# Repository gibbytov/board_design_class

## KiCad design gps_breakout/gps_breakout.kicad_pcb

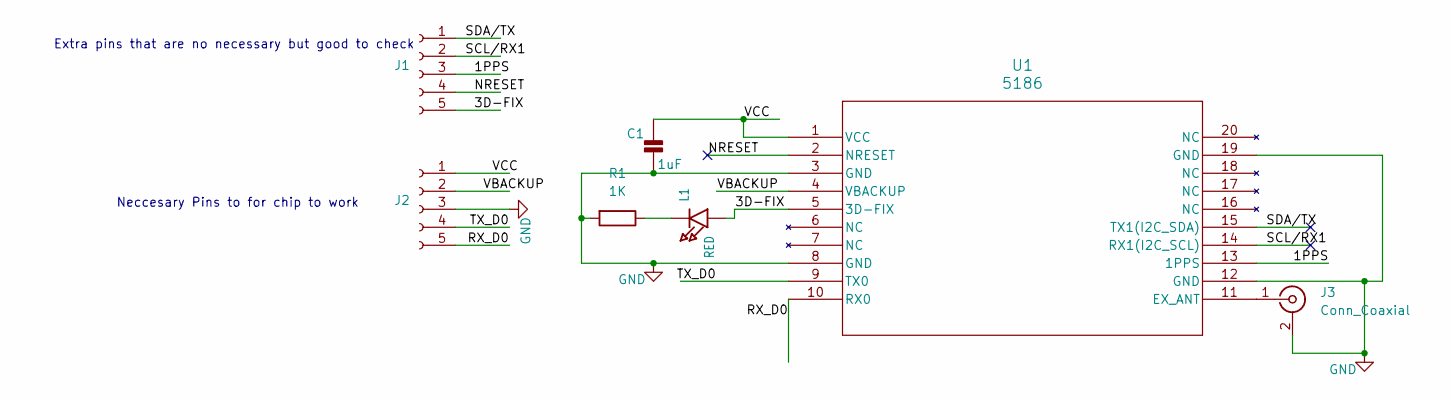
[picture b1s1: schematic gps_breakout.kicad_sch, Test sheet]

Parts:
C1: 1uF; C_0603_1608Metric_Pad1.08x0.95mm_HandSolder; Mfr P/N CC0603KRX7R7BB105
J1, J2: PinHeader_1x05_P2.54mm_Vertical; Mfr P/N M20-9772646
J3: Conn_Coaxial; SMA_Molex_73251-1153_EdgeMount_Horizontal; Mfr P/N CT-SAD12X-006M
L1: RED; CHIPLED_0805_NOOUTLINE; Mfr P/N LTST-S220KRKT
R1: 1K; RC0402N_YAG; Mfr P/N RC0402JR-071KL
U1: 5186; CD-PA1616D_ADA; Mfr P/N 5186

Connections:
/1PPS: J1.3, U1.13 (1PPS)
/3D-FIX: J1.5, L1.A, U1.5 (3D-FIX)
/NRESET: J1.4, U1.2 (NRESET)
/RX_D0: J2.5, U1.10 (RX0)
/SCL/RX1: J1.2, U1.14 (RX1(I2C_SCL))
/SDA/TX: J1.1, U1.15 (TX1(I2C_SDA))
/TX_D0: J2.4, U1.9 (TX0)
/VBACKUP: J2.2, U1.4 (VBACKUP)
/VCC: C1.1, J2.1, U1.1 (VCC)
GND: C1.2, J2.3, J3.2 (Ext), R1.2, U1.3 (GND), U1.8 (GND), U1.12 (GND), U1.19 (GND)
unnamed: J3.1 (In), U1.11 (EX_ANT)
unnamed: L1.C, R1.1

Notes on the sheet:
Extra pins that are no necessary but good to check
Neccesary Pins to for chip to work

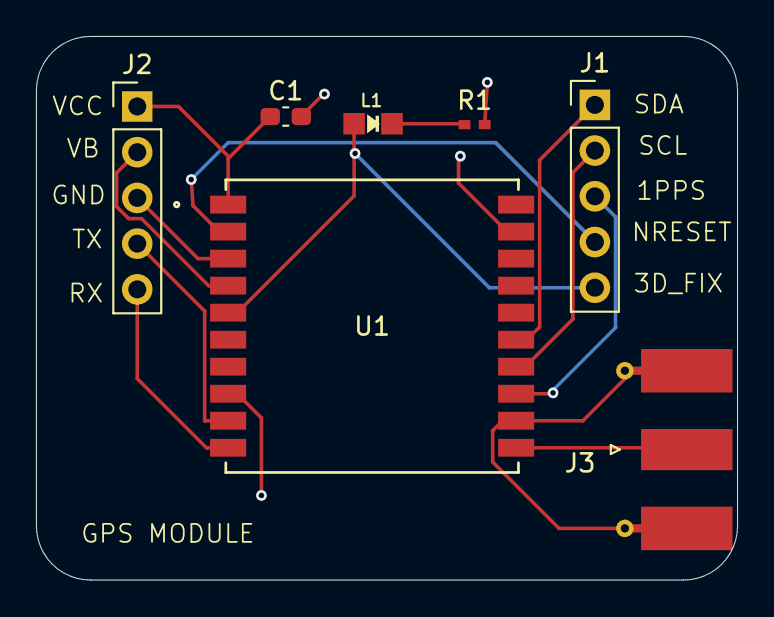
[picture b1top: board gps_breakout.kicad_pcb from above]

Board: 2 copper layers, 38.9 x 30.2 mm, 7 parts (0 on the bottom side), 12 nets.

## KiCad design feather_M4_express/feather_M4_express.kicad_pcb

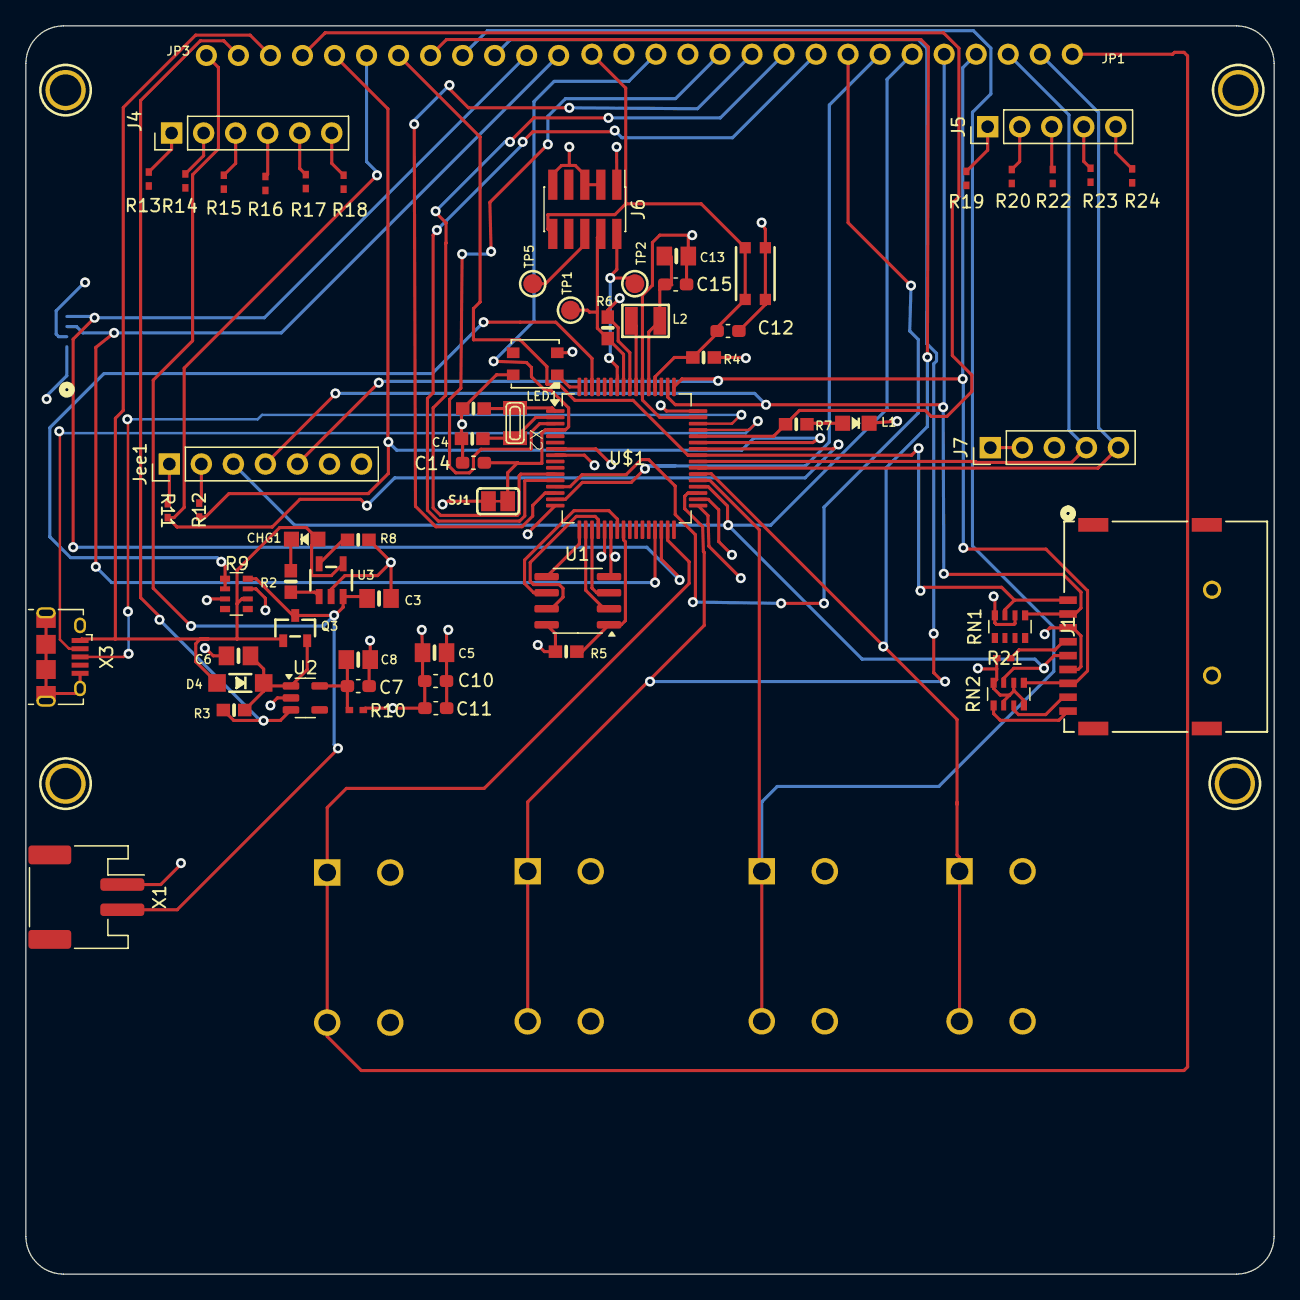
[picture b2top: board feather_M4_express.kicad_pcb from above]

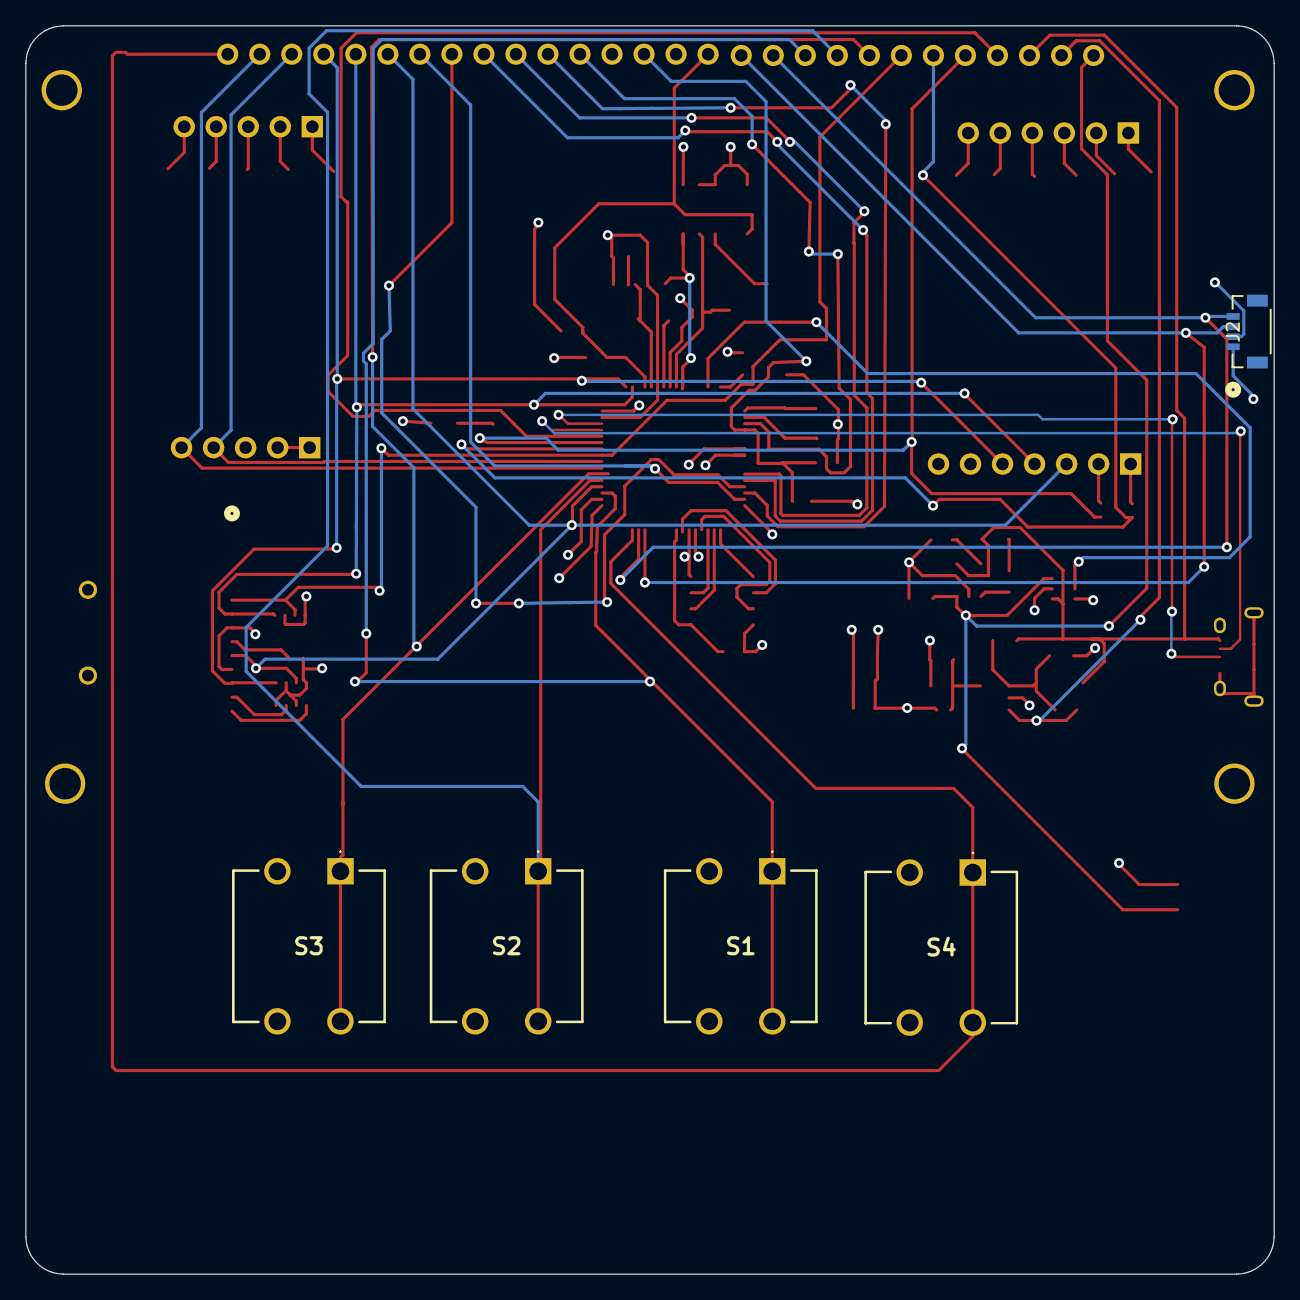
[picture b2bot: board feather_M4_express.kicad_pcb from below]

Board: 4 copper layers, 99.0 x 99.0 mm, 73 parts (5 on the bottom side), 67 nets.

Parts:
C2, C4: 22pF; 0603-NO
C3, C5, C6, C8, C13: 10µF; 0805-NO
C7, C10, C11, C12, C14, C15: 1uF; C_0603_1608Metric_Pad1.08x0.95mm_HandSolder
CHG1: ORANGE; CHIPLED_0805_NOOUTLINE
D4: MBR120; SOD-123
J1: MEM2075-00-140-01-A; MEM2075-00-140-01-A_GCT
J2: Conn_01x04; CONN4X1_DF52-4S-0.8H21_HIR
J4: Conn_01x06_Pin; PinHeader_1x06_P2.54mm_Vertical
J5, J7: Conn_01x05_Pin; PinHeader_1x05_P2.54mm_Vertical
J6: PinHeader_2x05_P1.27mm_Vertical_SMD
JP1: Conn_01x16; 1X16_ROUND
JP3: Conn_01x12; 1X12_ROUND
Jee1: Conn_01x07_Pin; PinHeader_1x07_P2.54mm_Vertical
L1: RED; CHIPLED_0805_NOOUTLINE
L2: 10uH; INDUCTOR_1007
LED1: WS2812B3535; LED3535
P$1, P$2, P$3, P$4: MountingHole; MOUNTINGHOLE_2.5_PLATED
Q3: DMP2070UQ-7; SOT23-R
R2: 1K; 0603-NO
R3, R4, R5, R6, R8: 10K; 0603-NO
R7: 2.2K; 0603-NO
R9: 100K; R_Array_Convex_4x0603
R10, R11, R12, R13, R14, R15, R16, R17, R18, R19, R20, R21, R22, R23, R24: 0 R; RES_1005_SAM
RN1, RN2: R_Pack04_SIP; R_Array_Convex_4x0603
S1, S2, S3, S4: PRT-14460; PRT14460
SJ1: SOLDERJUMPERCLOSED; SOLDERJUMPER_CLOSEDWIRE
SW1: KMR2; BTN_KMR2_4.6X2.8
TP1, TP2, TP5: TESTPOINTROUND1.5MM; TESTPOINT_ROUND_1.5MM
U1: 2MB Flash; SOIC-8_3.9x4.9mm_P1.27mm
U2: AP2112-3.3; SOT-23-5
U3: MCP73831T-2ACI/OT; SOT23-5
U$1: ATSAMD51J19A-AUT; TQFP-64_10x10mm_P0.5mm
X1: JSTPH; JST_PH_S2B-PH-SM4-TB_1x02-1MP_P2.00mm_Horizontal
X2: 32.768 kHz; XTAL3215
X3: microUSB 2.0 B; USB_Micro-B_Amphenol_10118194_Horizontal

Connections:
+3V3: C5.1, C10.1, C11.1, J2.2, J6.1, J7.1, J7.2, JP1.15, Jee1.7, LED1.2 (VDD), R4.1, R5.1, R6.1, R10.1, R21.1, RN1.6 (R3.2), RN1.8 (R4.2), RN2.2 (R1.2), RN2.4 (R2.2), RN2.6 (R3.2), RN2.8 (R4.2), SJ1.2, U1.8 (VCC), U$1.8 (VDDANA), U$1.16 (PA07/I7/AIN7/SERCOM0.3), U$1.21 (VDDIO_0), U$1.34 (VDDIO_1), U$1.48 (VDDIO_2), U$1.56 (VDDIO_3)
/1PPS: J5.3, R22.1
/3D-FIX: J5.5, R24.1
/A0: JP1.12, U$1.3 (PA02/EINT2/AIN0/VOUT0)
/A1: JP1.11, U$1.14 (PA05/I5/AIN5/VOUT1/SERCOM0.1)
/A2: JP1.10, U$1.11 (PB08/I8/AIN2/SERCOM4.0)
/A3: JP1.9, U$1.12 (PB09/I9/AIN3/SERCOM4.1)
/A4: JP1.8, U$1.13 (PA04/I4/VREFB/AIN4/SERCOM0.0)
/A5: JP1.7, U$1.15 (PA06/I6/VREFC/AIN6/SERCOM0.2)
/AREF: C14.1, JP1.14, SJ1.1, U$1.4 (PA03/I3/VREFA/AIN1)
/D4: JP1.1, S4.1, S4.2, U$1.31 (PA14/I14/SERCOM2+4.2)
/D5: JP3.10, S1.1, S1.2, U$1.35 (PA16/I2C/I0/SERCOM1.0+3.1)
/D6: JP3.9, S2.1, S2.2, U$1.37 (PA18/I2/SERCOM1+3.2)
/D8_NEOPIX: LED1.1 (DI), U$1.64 (PB03/I3/AIN15/SERCOM5.1)
/D9: JP3.8, S3.1, S3.2, U$1.38 (PA19/I3/SERCOM1+3.3)
/D10: J1.P1 (DAT2), JP3.7, RN1.7 (R4.1), U$1.41 (PA20/I4/SERCOM3+5.2/I2SFS0)
/D11: JP3.6, R11.2, U$1.42 (PA21/I5/SERCOM3+5.3/I2SDO)
/D12: JP3.5, R12.1, U$1.43 (PA22/I2C/16/SERCOM3.0+5.1/I2SDI)
/D13: JP3.4, R7.1, U$1.44 (PA23/I2C/I7/SERCOM3.1+5.0/SOF/I2SFS1)
/D+: U$1.46 (PA25/19/SERCOM3+5.3/D+), X3.3 (D+)
/D-: U$1.45 (PA24/I8/SERCOM3+5.2/D-), X3.2 (D-)
/EN: JP3.2, R3.2, U2.3 (EN)
/G1: J4.5, R17.1
/G2: J4.4, R16.1
/G3: J4.3, R15.1
/G4: J4.2, R14.1
/G5: J4.1, R13.1
/MISO: J1.P7 (DAT0), JP1.4, Jee1.5, RN2.5 (R3.1), U$1.49 (PB22/I6/SERCOM1+5.2)
/MOSI: J1.P2 (CD/DAT3), JP1.5, Jee1.4, RN1.5 (R3.1), U$1.50 (PB23/I7/SERCOM1+5.3)
/NRESET: J5.4, R23.1
/QSPI_CS: R5.2, U1.1 (SSEL), U$1.24 (PB11/I11/SERCOM4.3/I2SFS1)
/QSPI_DATA[0]: U1.5 (MOSI), U$1.17 (PA08/I2C/AIN8/SERCOM0.0+2.1/I2SMCK)
/QSPI_DATA[1]: U1.2 (MISO), U$1.18 (PA09/I2C/I9/AIN9/SERCOM0.1+2.0/I2SFS0)
/QSPI_DATA[2]: U1.3 (WP#/IO2), U$1.19 (PA10/I10/AIN10/SERCOM0+2.2/I2SCK)
/QSPI_DATA[3]: U1.7 (HOLD#/IO3), U$1.20 (PA11/I11/AIN11/SERCOM0+2.3/I2SDO)
/QSPI_SCK: U1.6 (SCK), U$1.23 (PB10/I10/SERCOM4.2/I2SDI)
/RST: J4.6, R18.1
/RX_D0: J7.4, JP1.3, U$1.40 (PB17/SERCOM5.1/I2SMCK0)
/SCK: J1.P5 (CLK), JP1.6, Jee1.3, RN2.7 (R4.1), U$1.36 (PA17/I2C/I1/SERCOM1.1+3.0)
/SCL: J2.4, JP3.11, U$1.30 (PA13/I13/I2C/SERCOM2.1+4.0)
/SCL/RX1: J5.2, R20.1
/SDA: J2.3, JP3.12, U$1.29 (PA12/I12/I2C/SERCOM2.0+4.1)
/SDA/TX: J5.1, R19.1
/SWCLK: J6.4, R6.2, TP1.P$1, U$1.57 (PA30/I14/SERCOM1.2/SWCLK)
/SWDIO: J6.2, TP2.P$1, U$1.58 (PA31/I15/SERCOM1.3/SWDIO)
/SWO: J6.6, TP5.P$1
/TX_D1: J7.5, JP1.2, U$1.39 (PB16/I0/SERCOM5.0/I2SCK0)
/V_DIV: R9.1, R9.2 (1), U$1.62 (PB01/I1/AIN13/SERCOM5.3)
/Vin: C6.1, D4.C, Q3.2 (S), R3.1, U2.1 (VIN)
/~RESET: C12.1, J6.10, JP1.16, R4.2, SW1.A, SW1.A' (P1), U$1.52 (~RESET)
GND: C2.2, C3.2, C4.2, C5.2, C6.2, C7.2, C8.2, C10.2, C11.2, C12.2, C13.2, C14.2, C15.2, J1.P3 (CMD), J1.P6 (VSS), J2.1, J6.3, J6.5, J6.9, J7.3, JP1.13, Jee1.6, L1.C, LED1.4 (GND), R8.2, R9.3 (1), R9.7 (2), S1.3, S1.4, S2.3, S2.4, S3.3, S3.4, S4.3, S4.4, SW1.B (S), SW1.B' (S1), U1.4 (VSS), U2.2 (GND), U3.2 (VSS), U$1.7 (GND_0), U$1.22 (GND_1), U$1.33 (GND_2), U$1.47 (GND_3), U$1.54 (GND_4), X1.1, X3.5 (GND), X3.6 (Shield)
unnamed: CHG1.C, R2.1
unnamed: J1.P9 (CD), RN2.1 (R1.1)
unnamed: J1.P8 (DAT1), RN2.3 (R2.1)
unnamed: J1.P4 (VDD), R21.2
unnamed: Jee1.1, R11.1
unnamed: Jee1.2, R12.2
unnamed: L1.A, R7.2
unnamed: C13.1, C15.1, L2.P$1 (1), U$1.53 (VDDCORE)
unnamed: L2.P$2 (2), U$1.55 (VSW)
unnamed: C7.1, C8.1, R10.2, U2.5 (VOUT)
unnamed: R8.1, U3.5 (PROG)
unnamed: R2.2, U3.1 (STAT)
unnamed: C2.1, U$1.1 (PA00/EINT0/SERCOM1.0), X2.P$1
unnamed: C4.1, U$1.2 (PA01/EINT1/SERCOM1.1), X2.P$2
VBAT: C3.1, JP3.1, Q3.3 (D), R9.8 (2), U3.3 (VBAT), X1.2
VBUS: CHG1.A, D4.A, JP3.3, Q3.1 (G), R9.6 (2), U3.4 (VDD), X3.1 (VBUS)

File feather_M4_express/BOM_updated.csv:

"Reference","Value","Qty","DNP","Mfr","Mfr P/N","Supplier_1","Supplier_1 P/N","Supplier_1 Unit Price","Supplier 1","Supplier 1 P/N","Supplier 1 Price @ Qty"
"C2,C4","22pF","2","","KEMET","C0603C220K4GAC7867","Digikey","399-C0603C220K4GAC7867CT-ND","0.10","","",""
"C3,C5,C6,C8,C13","10µF","5","","Samsung Electro-Mechanics","CL21A106KOQNNNE","Digikey","1276-1096-1-ND","0.10","","",""
"C7,C10,C11,C12,C14,C15","1uF","6","","YAGEO","CC0603KRX7R7BB105","Digikey","311-1446-1-ND","0.10","","",""
"CHG1","ORANGE","1","","Harvatek Corporation","B1701UD--20D000414U1930","Digikey","3147-B1701UD--20D000414U1930CT-ND","0.10","","",""
"D4","MBR120","1","","onsemi","MBR120LSFT1G","Digikey","MBR120LSFT1GOSCT-ND","0.42","","",""
"J1","-- mixed values --","1","","-- mixed values --","-- mixed values --","","","","DigiKey","-- mixed values --","-- mixed values --"
"J2","Conn_01x04","1","","Hirose Electric Co Ltd","DF52-4S-0.8H(21)","","","","DigiKey","H125098CT-ND",".34"
"J4","Conn_01x06_Pin","1","","Sullins Connector Solutions","PPTC061LFBN-RC","","","","Digikey","S7004-ND",".61"
"J5,J7","Conn_01x05_Pin","2","","Sullins Connector Solutions","PPTC051LFBN-RC","","","","DigiKey","S6103-ND",".57"
"J6","~","1","","CNC Tech","3221-10-0100-00","","","","Digikey ","1175-1733-ND","0.71"
"L1","RED","1","","Lite-On Inc.","LTST-S220KRKT","Digikey","160-1469-1-ND","0.23","","",""
"L2","10uH","1","","Taiyo Yuden","LSQEA251818T100K","Digikey","587-LSQEA251818T100KCT-ND","0.13","","",""
"LED1","WS2812B3535","1","","DONGGUANG OPSCO OPTOELECTRONICS CO., LTD","SK6812MINI","Adafruit","2686","0.495","","",""
"Q3","DMP2070UQ-7","1","","Diodes Incorporated","DMP2070UQ-7","Digikey","31-DMP2070UQ-7CT-ND","0.48","","",""
"R1,R10,R11,R12,R13,R14,R15,R16,R17,R18,R19,R20,R21,R22,R23,R24","0 R","16","","Samsung Electro-Mechanics","RC1005J000CS","","","","DigiKey","1276-3480-1-ND","0.029"
"R2","1K","1","","Vishay Beyschlag/Draloric/BC Components","MCT06030C1001FP500","Digikey","MCT0603-1.00K-CFCT-ND","0.10","","",""
"R3,R4,R5,R6,R8","10K","5","","Stackpole Electronics Inc","RNCP0603FTD10K0","Digikey","RNCP0603FTD10K0CT-ND","0.10","","",""
"R7","2.2K","1","","TE Connectivity Passive Product","CRGH0603F2K2","Digikey","A129540CT-ND","0.10","","",""
"R9","100K","1","","Bourns Inc.","CAY16-1003F4LF","Digikey","CAY16-1003F4LFCT-ND","0.10","","",""
"RN1,RN2","R_Pack04_SIP","2","","-- mixed values --","YC164-JR-0747KL","","","","DigiKey","YC164J-47KCT-ND",".10"
"S1,S2,S3,S4","PRT-14460","4","","-- mixed values --","PRT-14460","","","","DigiKey","1568-1757-ND","1.75"
"SW1","KMR2","1","","C&K","KMR241NG ULC LFS","Digikey","CKN10285CT-ND","0.92","","",""
"U$1","ATSAMD51J19A-AUT","1","","Microchip Technology","ATSAMD51J19A-AUT","Digikey","ATSAMD51J19A-AUTCT-ND","5.68","","",""
"U1","2MB Flash","1","","GigaDevice Semiconductor (HK) Limited","GD25Q16ETIGR","Digikey","1970-GD25Q16ETIGRCT-ND","0.74","","",""
"U2","AP2112-3.3","1","","Diodes Incorporated","AP2112K-3.3TRG1","Digikey","AP2112K-3.3TRG1DICT-ND","0.35","","",""
"U3","MCP73831T-2ACI/OT","1","","Microchip Technology","MCP73831T-2ATI/OT","Digikey","MCP73831T-2ATI/OTCT-ND","0.76","","",""
"X1","JSTPH","1","","JST Sales America Inc.","S2B-PH-SM4-TB","Digikey","455-S2B-PH-SM4-TBCT-ND","0.58","","",""
"X2","32.768 kHz","1","","NDK America, Inc.","STDMUA17-32.768K","Digikey","644-STDMUA17-32.768KCT-ND","1.02","","",""
"X3","microUSB 2.0 B","1","","Amphenol ICC (FCI)","10118194-0001LF","Digikey","609-4618-1-ND","0.57","","",""

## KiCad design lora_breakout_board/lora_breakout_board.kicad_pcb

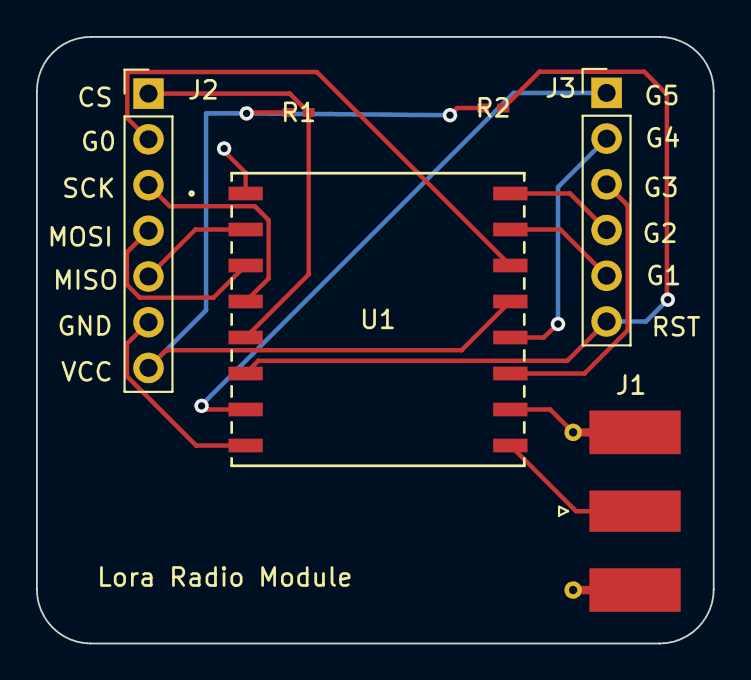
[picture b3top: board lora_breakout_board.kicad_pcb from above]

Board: 2 copper layers, 37.6 x 33.7 mm, 6 parts (0 on the bottom side), 14 nets.

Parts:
J1: Conn_Coaxial; SMA_Molex_73251-1153_EdgeMount_Horizontal
J2: Conn_01x07_Socket; PinHeader_1x07_P2.54mm_Vertical
J3: Conn_01x06_Socket; PinHeader_1x06_P2.54mm_Vertical
R1, R2: 100K; RC0402N_YAG
U1: COM-13909; RFM69HCW_SPK

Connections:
/CS: J2.1, R1.2, U1.5 (NSS)
/G0: J2.2, U1.14 (DIO0)
/G1: J3.5, U1.15 (DIO1)
/G2: J3.4, U1.16 (DIO2)
/G3: J3.3, U1.11 (DIO3)
/G4: J3.2, U1.12 (DIO4)
/G5: J3.1, U1.7 (DIO5)
/MISO: J2.5, U1.2 (MISO)
/MOSI: J2.4, U1.3 (MOSI)
/RESET: J3.6, R2.2, U1.6 (RESET)
/SCK: J2.3, U1.4 (SCK)
/VCC: J2.7, R1.1, R2.1, U1.13 (3.3V)
GND: J1.2 (Ext), J2.6, U1.1 (GND), U1.8 (GND), U1.10 (GND)
unnamed: J1.1 (In), U1.9 (ANT)

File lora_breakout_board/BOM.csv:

"Reference","Value","Qty","DNP","Supplier 1","Supplier 1 P/N","Supplier 1 Price @ Qty","Supplier 1 Unit Price"
"J1","Conn_Coaxial","1","","DigiKey","5448-CT-SAD12X-006M-ND","2.62","2.62"
"R1,R2","100K","2","","DigiKey","1276-3480-1-ND","0.029",".10"
"U1","COM-13909","1","","Sparkfun","RFM69HCW Wireless Transceiver - 915MHz","6.50","6.50"

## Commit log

2024-12-30 upload only code
2024-12-30 Add files via upload
    adding breakout board files
2024-12-30 modified M4 files
2024-12-30 Add files via upload
    Project summary/report
